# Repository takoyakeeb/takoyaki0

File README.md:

# takoyaki0 entry

入門用(entry)の8キーのキーボードです。takoyakeeb の機種の1つです。

- キー: MX スイッチ 8個(4×2)、ホットスワップ
- マイコン: Waveshare RP2040-Zero(ピンヘッダーで取り付け)
- 部品はスルーホールが中心で、ハンダ付けが初めての人でも組み立てやすい形を目指しています

**いまの状態: 設計中です。** まだ組み立てられません。

## ライセンス

Copyright (c) 2026 takoyakeeb
SPDX-License-Identifier: CERN-OHL-P-2.0

このリポジトリの中身(基板の設計データと文書)は、CERN-OHL-P-2.0(CERN Open Hardware Licence Version 2 - Permissive)です。全文は `LICENSE` を見てください。

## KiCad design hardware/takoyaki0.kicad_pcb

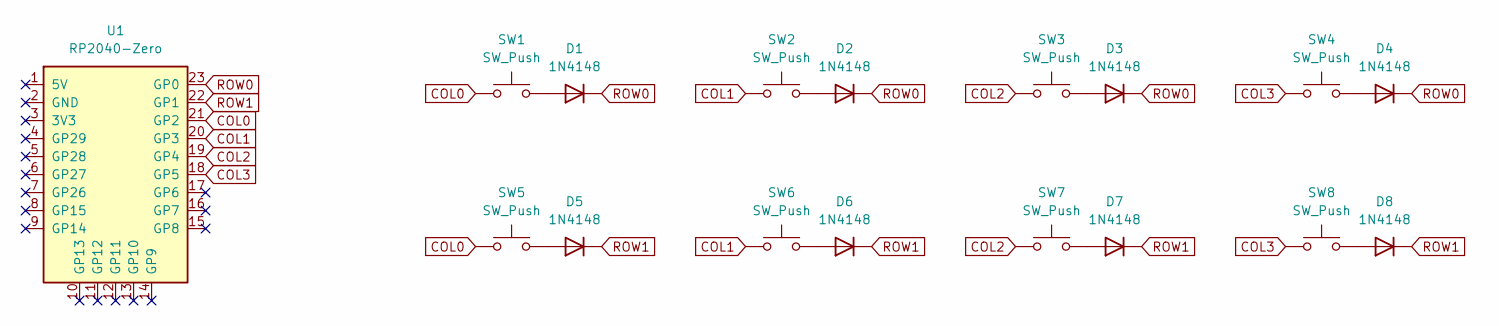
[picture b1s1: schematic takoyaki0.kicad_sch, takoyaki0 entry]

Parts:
D1, D2, D3, D4, D5, D6, D7, D8: 1N4148; D_DO-35_SOD27_P7.62mm_Horizontal
SW1, SW2, SW3, SW4, SW5, SW6, SW7, SW8: SW_Push; SW_MX_HS_CPG151101S11_1u
U1: RP2040-Zero; RP2040-Zero_PinHeader

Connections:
COL0: SW1.1, SW5.1, U1.21 (GP2)
COL1: SW2.1, SW6.1, U1.20 (GP3)
COL2: SW3.1, SW7.1, U1.19 (GP4)
COL3: SW4.1, SW8.1, U1.18 (GP5)
unnamed: D1.2 (A), SW1.2
unnamed: D2.2 (A), SW2.2
unnamed: D3.2 (A), SW3.2
unnamed: D4.2 (A), SW4.2
unnamed: D5.2 (A), SW5.2
unnamed: D6.2 (A), SW6.2
unnamed: D7.2 (A), SW7.2
unnamed: D8.2 (A), SW8.2
ROW0: D1.1 (K), D2.1 (K), D3.1 (K), D4.1 (K), U1.23 (GP0)
ROW1: D5.1 (K), D6.1 (K), D7.1 (K), D8.1 (K), U1.22 (GP1)

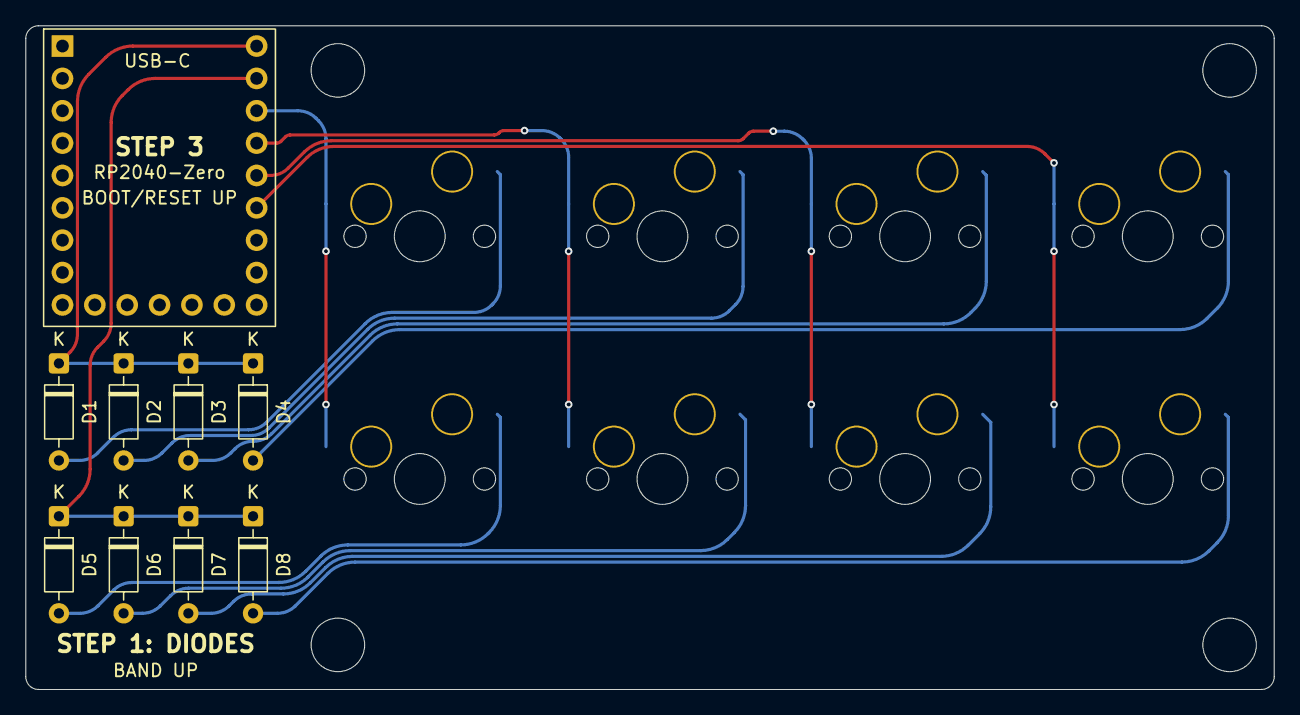
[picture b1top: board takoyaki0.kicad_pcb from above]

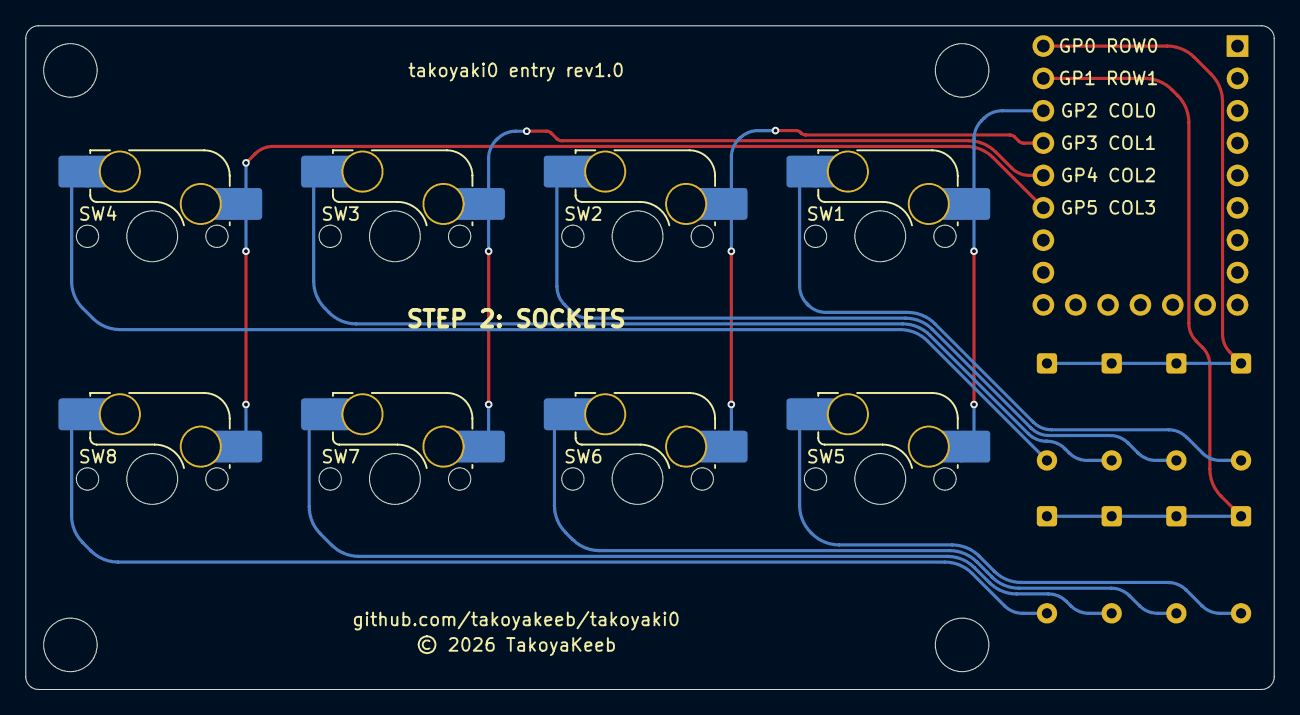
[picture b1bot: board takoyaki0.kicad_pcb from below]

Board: 2 copper layers, 98.0 x 52.1 mm, 17 parts (8 on the bottom side), 14 nets.

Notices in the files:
hardware/takoyaki0.kicad_pcb:
© 2026 TakoyaKeeb
